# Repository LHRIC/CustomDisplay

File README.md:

# Custom Display

##Purpose

Custom Display is a driver information display for the car, built on an STM32H7 microcontroller with a Riverdi LCD. The STM32 reads live data from the Haltech ECU over the car's CAN bus and renders it on-screen using [TouchGFX](https://support.touchgfx.com/docs/introduction/what-is-touchgfx), an embedded graphics library for STM32.

**Display hardware:** [https://riverdi.com/product/5-inch-tft-lcd-screen-stm32u5-embedded-display-rvt50hqsfwn01?srsltid=AfmBOoq_PbYSuQUkMhpmtfA5kOqO7L9fX0RrjbtiRxhyNDaXJeP7M8Rh](#)  
> 

---

## Overview

| Detail | Value |
|---|---|
| Microcontroller | STM32H7 |
| Display | Riverdi LCD |
| Graphics Library | TouchGFX |
| Language | C / C++ |
| RTOS | None (simplified loop via `Model::tick`) |
| Data Source | ECU via CAN bus |

---

## Architecture

All code is written in C style but integrates with TouchGFX, a C++ library. There is no RTOS — the update loop runs entirely inside `Model::tick` for simplicity.

### Data Flow

```
CAN Bus (mostly ECU though it can be anything on CAN bus)
    │
    ▼
CAN Interrupt (main.c)
    │  updates
    ▼
can_types.cpp  ──  UI data elements & handlers
-----
Model.cpp      ──  data update tick
    │
    ▼
Screen1Presenter.cpp
    │
    ▼
Screen1View.cpp  ──  UI element rendering
```

### Key Files

| File | Role |
|---|---|
| `main.c` | CAN interrupt setup; `RxFifo0Callback` routes incoming CAN frames |
| `can_types.hpp` | Declares CAN value types, IDs, default values, etc|
| `can_types.cpp` | Defines CAN values and the `CAN_value_ptrs` array |
| `Model.cpp` | Polls updated CAN data each tick and forwards to presenter |
| `Screen1Presenter.cpp` | Mediates between model and view |
| `Screen1View.cpp` | Updates UI elements; handles special visual logic |

---

## Contributing

The TouchGFX tutorials and docs are pretty good for understanding how it works. Also, I used CubeMX to generate code, TouchGFX Designer to generate UI code, CMake to build, and VSCode Arm Cortex Debug for flash/debug.

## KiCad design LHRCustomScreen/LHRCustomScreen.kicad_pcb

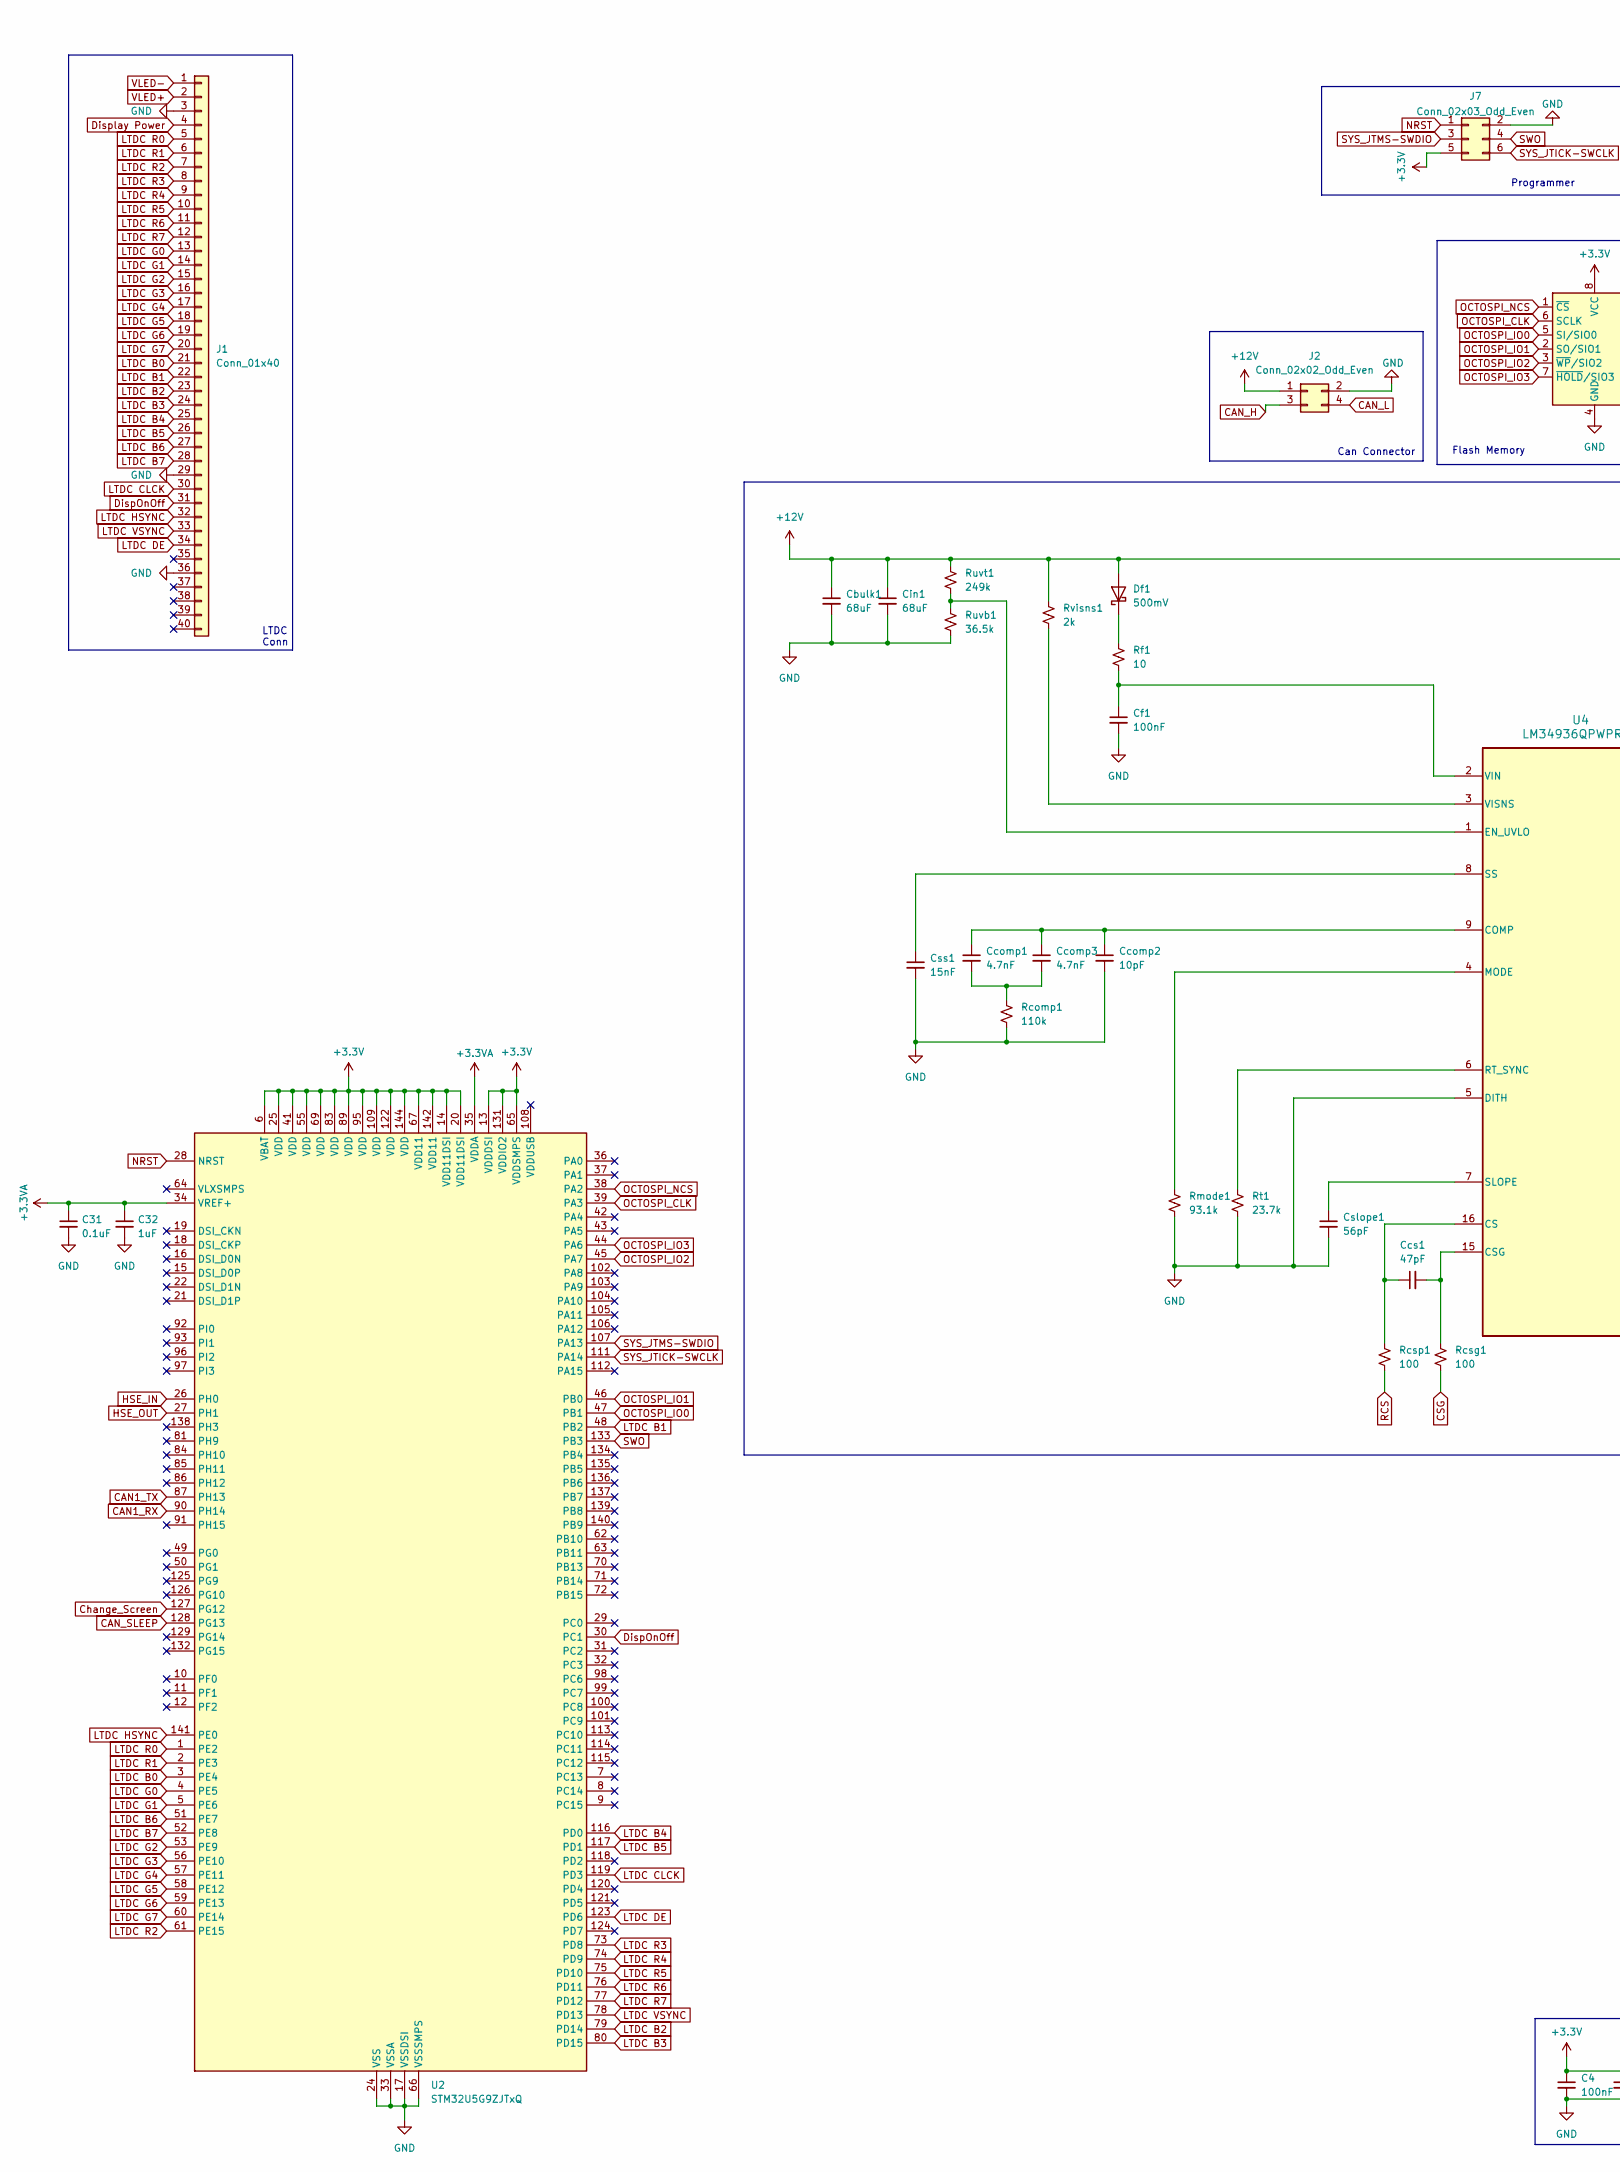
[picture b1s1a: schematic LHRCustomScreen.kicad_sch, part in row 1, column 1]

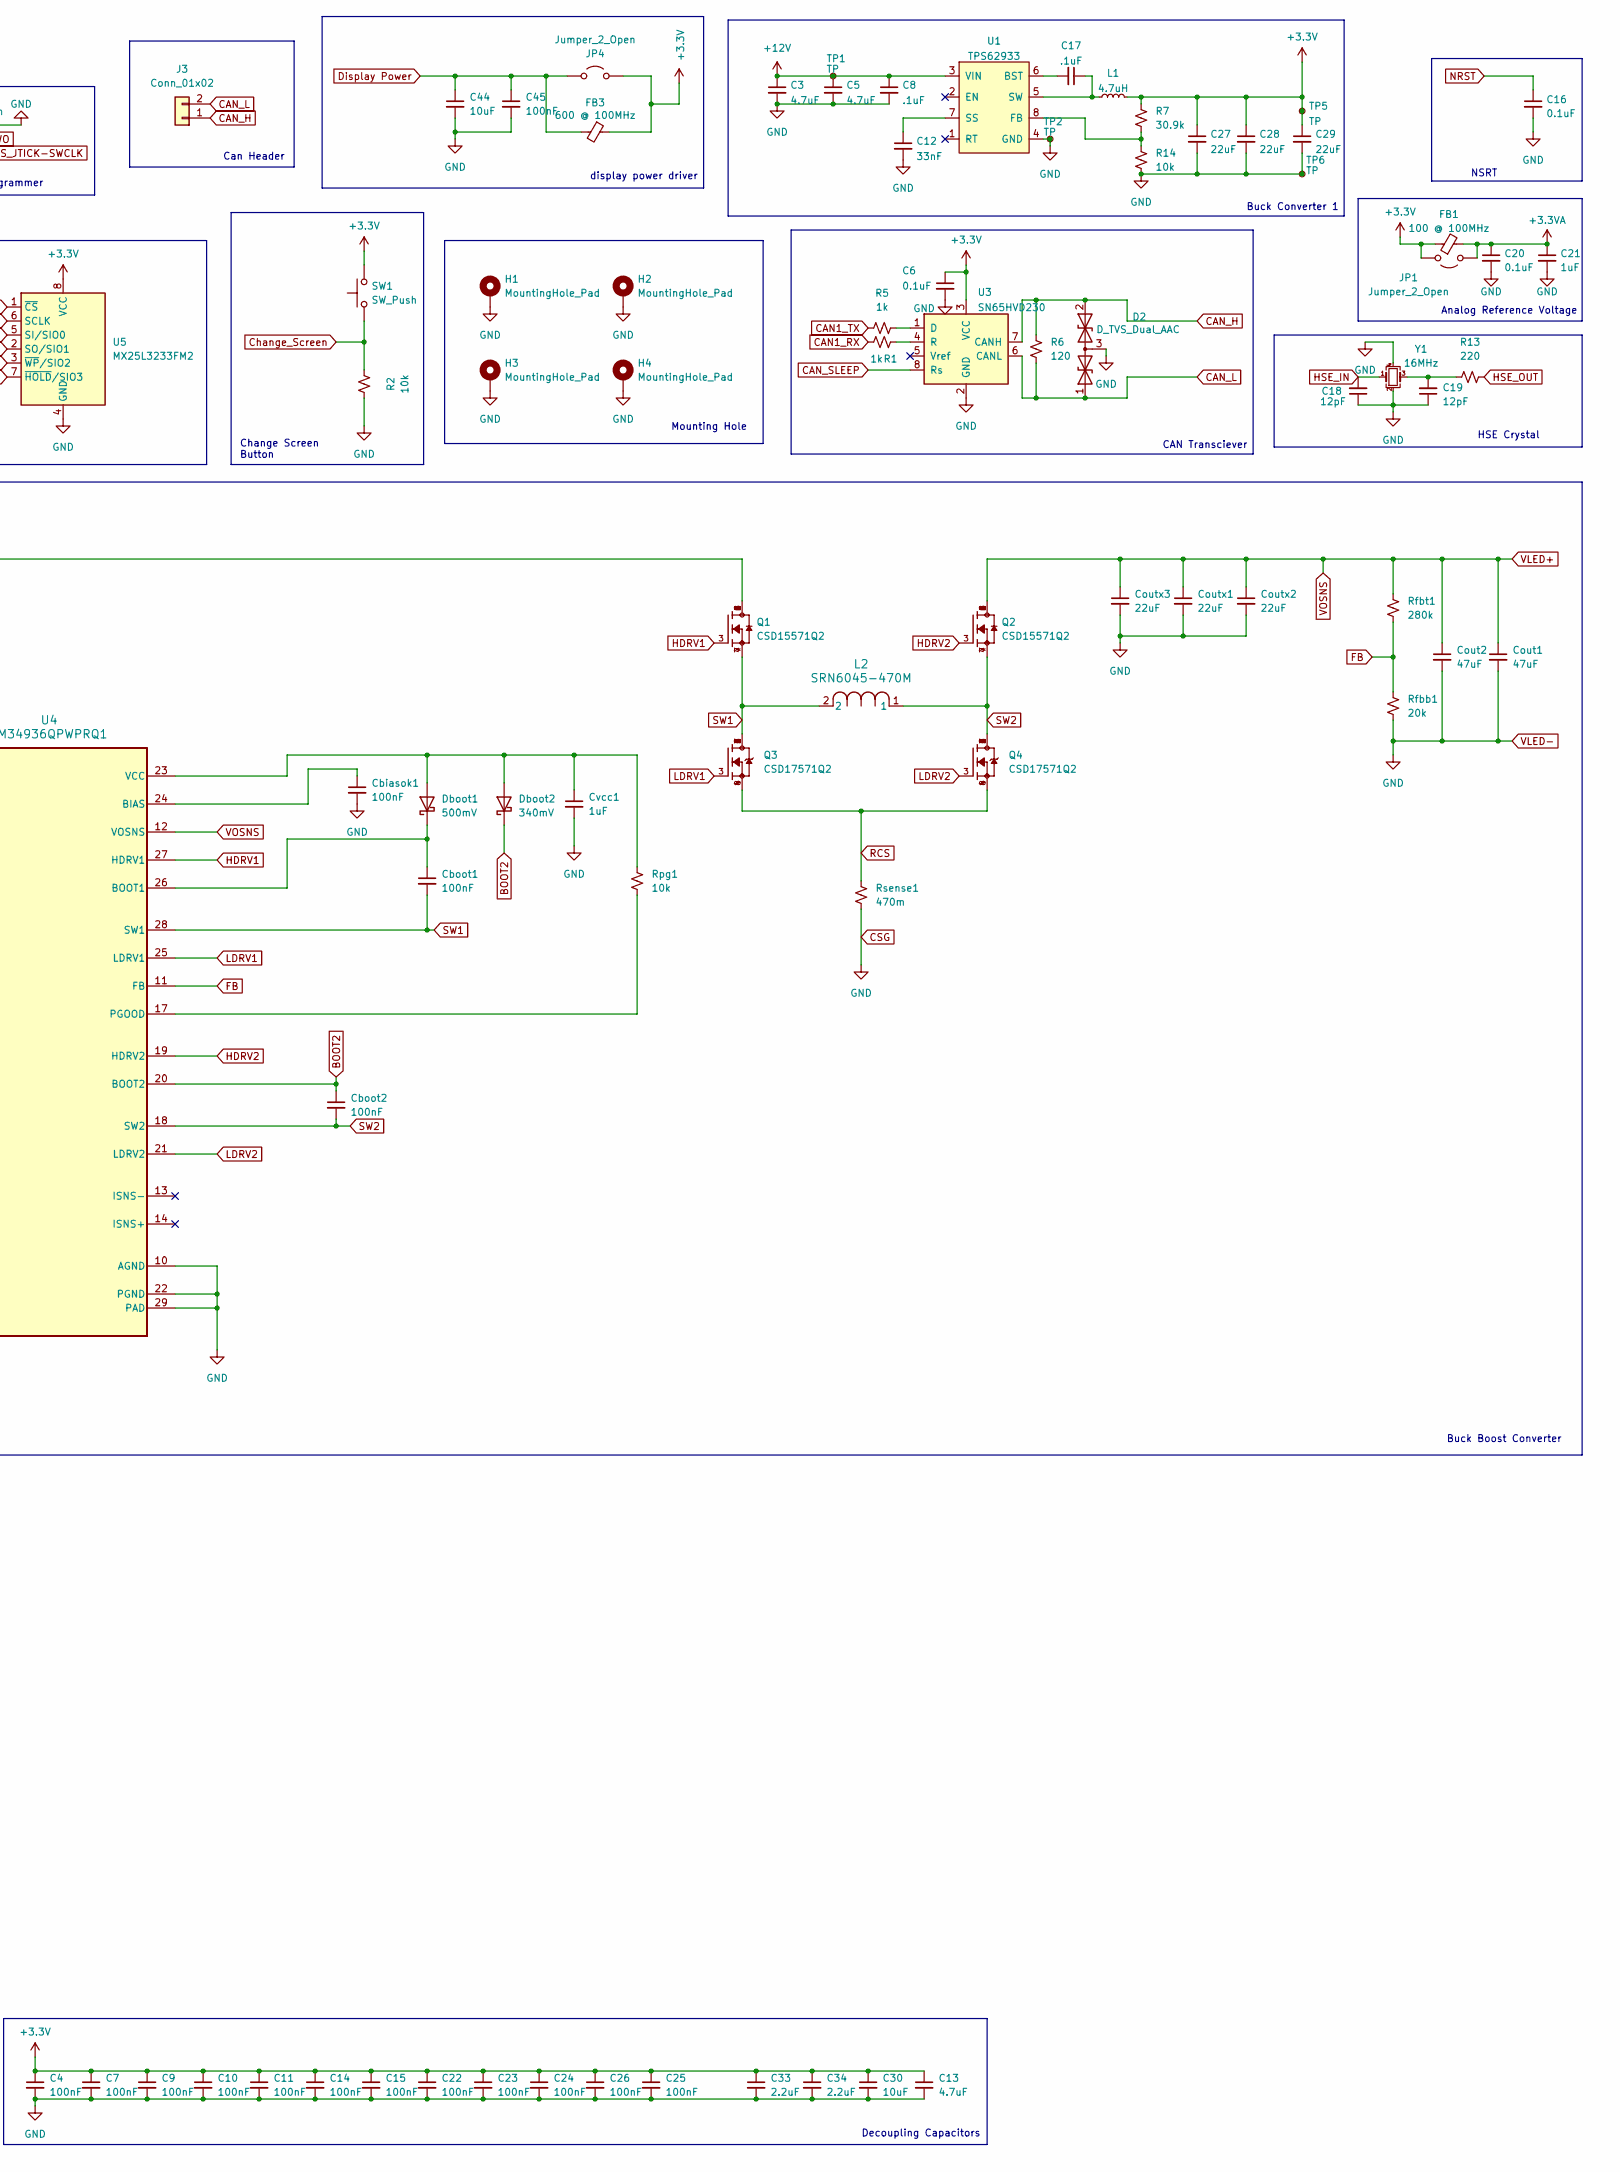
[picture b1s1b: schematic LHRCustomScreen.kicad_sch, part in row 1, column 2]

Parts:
C3, C5, C13: 4.7uF; C_0805_2012Metric
C4, C7, C9, C10, C11, C14, C15, C22, C23, C24, C25, C26, C45: 100nF; C_0603_1608Metric
C6, C20, C31: 0.1uF; C_0603_1608Metric
C8, C17: .1uF; C_0603_1608Metric
C12: 33nF; C_0603_1608Metric
C16: 0.1uF; C_0402_1005Metric
C18, C19: 12pF; C_0402_1005Metric
C21, C32: 1uF; C_0603_1608Metric
C27, C28, C29: 22uF; C_0805_2012Metric
C30, C44: 10uF; C_0805_2012Metric
C33, C34: 2.2uF; C_0603_1608Metric
Cbiasok1: 100nF; C_0805_2012Metric
Cboot1, Cboot2: 100nF; C_0603_1608Metric
Cbulk1: 68uF; PCAP_6.3x7.7-ELECT_NCA
Ccomp1, Ccomp3: 4.7nF; C_0201_0603Metric
Ccomp2: 10pF; C_0805_2012Metric
Ccs1: 47pF; C_0603_1608Metric
Cf1: 100nF; C_0603_1608Metric
Cin1: 68uF; PCAP_6.3x7.7-ELECT_NCA
Cout1, Cout2: 47uF; CAPC3225X270N
Coutx1, Coutx2, Coutx3: 22uF; C_0805_2012Metric
Cslope1: 56pF; C_0201_0603Metric
Css1: 15nF; C_0603_1608Metric
Cvcc1: 1uF; C_0603_1608Metric
D2: D_TVS_Dual_AAC; SOT-23
Dboot1: 500mV; DO-214AC_VIS
Dboot2: 340mV; DIOM3616X98N
Df1: 500mV; DO-214AC_VIS
FB1: 100 @ 100MHz; C_0402_1005Metric
FB3: 600 @ 100MHz; BEADC1608X95N
H1, H2, H3, H4: MountingHole_Pad; MountingHole_3.2mm_M3_DIN965_Pad_TopBottom
J1: Conn_01x40; FPC_40
J2: Conn_02x02_Odd_Even; ATM15-4P-BM03
J3: Conn_01x02; PinHeader_1x02_P2.54mm_Vertical
J7: Conn_02x03_Odd_Even; Molex_Micro-Fit_3.0_43045-0612_2x03_P3.00mm_Vertical
JP1, JP4: Jumper_2_Open; SolderJumper-2_P1.3mm_Bridged_RoundedPad1.0x1.5mm
L1: 4.7uH; SRU8043-4R7Y
L2: SRN6045-470M; IND_BOURNS_SRN6045
Q1, Q2: CSD15571Q2; TRANS_CSD15571Q2; PARTREV D
Q3, Q4: CSD17571Q2; TRANS_CSD17571Q2; PARTREV A
R1, R5: 1k; R_0603_1608Metric
R2, R14: 10k; R_0603_1608Metric
R6: 120; R_0603_1608Metric
R7: 30.9k; R_0603_1608Metric
R13: 220; R_0603_1608Metric
Rcomp1: 110k; R_0402_1005Metric
Rcsg1: 100; R_0603_1608Metric
Rcsp1: 100; R_0603_1608Metric
Rf1: 10; R_0603_1608Metric
Rfbb1: 20k; R_0603_1608Metric
Rfbt1: 280k; R_0603_1608Metric
Rmode1: 93.1k; R_0603_1608Metric
Rpg1: 10k; R_0603_1608Metric
Rsense1: 470m; R_0603_1608Metric
Rt1: 23.7k; R_0603_1608Metric
Ruvb1: 36.5k; R_0603_1608Metric
Ruvt1: 249k; R_0603_1608Metric
Rvisns1: 2k; R_0402_1005Metric
SW1: SW_Push; SW_PUSH_6mm
TP1, TP2, TP5, TP6: TP; TestPoint_Pad_D2.0mm
U1: TPS62933; SOT-583
U2: STM32U5G9ZJTxQ; LQFP-144_20x20mm_P0.5mm
U3: SN65HVD230; SOIC-8_3.9x4.9mm_P1.27mm
U4: LM34936QPWPRQ1; PWP0028C_N
U5: MX25L3233FM2; SOIC-8_5.3x5.3mm_P1.27mm
Y1: 16MHz; Crystal_SMD_3225-4Pin_3.2x2.5mm

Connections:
+3.3V: C4.1, C6.1, C7.1, C9.1, C10.1, C11.1, C13.1, C14.1, C15.1, C22.1, C23.1, C24.1, C25.1, C26.1, C27.1, C28.1, C29.1, C30.1, C33.1, C34.1, FB1.1, FB3.1, J7.5, JP1.2 (B), JP4.2 (B), L1.2, R7.1, SW1.2, TP5.1, U2.6 (VBAT), U2.13 (VDDDSI), U2.14 (VDD11DSI), U2.20 (VDD11DSI), U2.25 (VDD), U2.41 (VDD), U2.55 (VDD), U2.65 (VDDSMPS), U2.67 (VDD11), U2.69 (VDD), U2.83 (VDD), U2.89 (VDD), U2.95 (VDD), U2.109 (VDD), U2.122 (VDD), U2.131 (VDDIO2), U2.142 (VDD11), U2.144 (VDD), U3.3 (VCC), U5.8 (VCC); also elsewhere on the board
+3.3VA: C20.1, C21.1, C31.1, C32.1, FB1.2, JP1.1 (A), U2.34 (VREF+), U2.35 (VDDA)
+12V: C3.1, C5.1, C8.1, Cbulk1.1, Cin1.1, Df1.2 (A), J2.1, Q1.1, Q1.2, Q1.5, Q1.6, Q1.8, Ruvt1.1, Rvisns1.1, TP1.1, U1.3 (VIN); also elsewhere on the board
BOOT2: Cboot2.1, Dboot2.1 (K), U4.20 (BOOT2)
CAN1_RX: R1.2, U2.90 (PH14)
CAN1_TX: R5.1, U2.87 (PH13)
CAN_H: D2.2 (A2), J2.3, J3.1, R6.2, U3.7 (CANH)
CAN_L: D2.1 (A1), J2.4, J3.2, R6.1, U3.6 (CANL)
CAN_SLEEP: U2.128 (PG13), U3.8 (Rs)
CSG: C3.2, C4.2, C5.2, C6.2, C7.2, C8.2, C9.2, C10.2, C11.2, C12.2, C13.2, C14.2, C15.2, C16.2, C18.1, C19.1, C20.2, C21.2, C22.2, C23.2, C24.2, C25.2, C26.2, C27.2, C28.2, C29.2, C30.2, C31.2, C32.2, C33.2, C34.2, C44.2, C45.2, Cbiasok1.2, Cbulk1.2, Ccomp2.2, Cf1.2, Cin1.2, Cout1.2, Cout2.2, Coutx1.2, Coutx2.2, Coutx3.2, Cslope1.2, Css1.2, Cvcc1.2, D2.3 (common), H1.1, H2.1, H3.1, H4.1, J1.1, J1.3, J1.29, J1.36, J2.2, J7.2, R2.1, R14.2, Rcomp1.2, Rcsg1.2, Rfbb1.2, Rmode1.2, Rsense1.2, Rt1.2, Ruvb1.2, TP2.1, TP6.1, U1.4 (GND), U2.17 (VSSDSI), U2.23 (VSSDSI), U2.24 (VSS), U2.33 (VSSA), U2.40 (VSS), U2.54 (VSS), U2.66 (VSSSMPS), U2.68 (VSS), U2.82 (VSS), U2.88 (VSS), U2.94 (VSS), U2.110 (VSS), U2.130 (VSS), U2.143 (VSS), U3.2 (GND), U4.5 (DITH), U4.10 (AGND), U4.22 (PGND), U4.29 (PAD), U5.4 (GND), Y1.2, Y1.4; also elsewhere on the board
Change_Screen: R2.2, SW1.1, U2.127 (PG12)
DispOnOff: J1.31, U2.30 (PC1)
Display Power: C44.1, C45.1, FB3.2, J1.4, JP4.1 (A)
FB: Rfbb1.1, Rfbt1.2, U4.11 (FB)
HDRV1: Q1.3, U4.27 (HDRV1)
HDRV2: Q2.3, U4.19 (HDRV2)
HSE_IN: C18.2, U2.26 (PH0), Y1.1
HSE_OUT: R13.2, U2.27 (PH1)
LDRV1: Q3.3, U4.25 (LDRV1)
LDRV2: Q4.3, U4.21 (LDRV2)
LTDC B0: J1.21, U2.3 (PE4)
LTDC B1: J1.22, U2.48 (PB2)
LTDC B2: J1.23, U2.79 (PD14)
LTDC B3: J1.24, U2.80 (PD15)
LTDC B4: J1.25, U2.116 (PD0)
LTDC B5: J1.26, U2.117 (PD1)
LTDC B6: J1.27, U2.51 (PE7)
LTDC B7: J1.28, U2.52 (PE8)
LTDC CLCK: J1.30, U2.119 (PD3)
LTDC DE: J1.34, U2.123 (PD6)
LTDC G0: J1.13, U2.4 (PE5)
LTDC G1: J1.14, U2.5 (PE6)
LTDC G2: J1.15, U2.53 (PE9)
LTDC G3: J1.16, U2.56 (PE10)
LTDC G4: J1.17, U2.57 (PE11)
LTDC G5: J1.18, U2.58 (PE12)
LTDC G6: J1.19, U2.59 (PE13)
LTDC G7: J1.20, U2.60 (PE14)
LTDC HSYNC: J1.32, U2.141 (PE0)
LTDC R0: J1.5, U2.1 (PE2)
LTDC R1: J1.6, U2.2 (PE3)
LTDC R2: J1.7, U2.61 (PE15)
LTDC R3: J1.8, U2.73 (PD8)
LTDC R4: J1.9, U2.74 (PD9)
LTDC R5: J1.10, U2.75 (PD10)
LTDC R6: J1.11, U2.76 (PD11)
LTDC R7: J1.12, U2.77 (PD12)
LTDC VSYNC: J1.33, U2.78 (PD13)
NRST: C16.1, J7.1, U2.28 (NRST)
unnamed: C19.2, R13.1, Y1.3
unnamed: Ccomp1.2, Ccomp3.2, Rcomp1.1
unnamed: Cvcc1.1, Dboot1.2 (A), Dboot2.2 (A), Rpg1.1, U4.23 (VCC)
unnamed: Cboot1.1, Dboot1.1 (K), U4.26 (BOOT1)
unnamed: Df1.1 (K), Rf1.1
unnamed: C17.2, U1.6 (BST)
unnamed: R7.2, R14.1, U1.8 (FB)
unnamed: C12.1, U1.7 (SS)
unnamed: C17.1, L1.1, U1.5 (SW)
unnamed: R5.2, U3.1 (D)
unnamed: R1.1, U3.4 (R)
unnamed: Cbiasok1.1, U4.24 (BIAS)
unnamed: Ccomp1.1, Ccomp2.1, Ccomp3.1, U4.9 (COMP)
unnamed: Ccs1.1, Rcsp1.1, U4.16 (CS)
unnamed: Ccs1.2, Rcsg1.1, U4.15 (CSG)
unnamed: Ruvb1.1, Ruvt1.2, U4.1 (EN_UVLO)
unnamed: Rmode1.1, U4.4 (MODE)
unnamed: Rpg1.2, U4.17 (PGOOD)
unnamed: Rt1.1, U4.6 (RT_SYNC)
unnamed: Cslope1.1, U4.7 (SLOPE)
unnamed: Css1.1, U4.8 (SS)
unnamed: Cf1.1, Rf1.2, U4.2 (VIN)
unnamed: Rvisns1.2, U4.3 (VISNS)
OCTOSPI_CLK: U2.39 (PA3), U5.6 (SCLK)
OCTOSPI_IO0: U2.47 (PB1), U5.5 (SI/SIO0)
OCTOSPI_IO1: U2.46 (PB0), U5.2 (SO/SIO1)
OCTOSPI_IO2: U2.45 (PA7), U5.3 (~WP/SIO2)
OCTOSPI_IO3: U2.44 (PA6), U5.7 (~HOLD/SIO3)
OCTOSPI_NCS: U2.38 (PA2), U5.1 (~CS)
RCS: Q3.4, Q3.8, Q4.4, Q4.8, Rcsp1.2, Rsense1.1
SW1: Cboot1.2, L2.2, Q1.4, Q1.7, Q3.1, Q3.2, Q3.5, Q3.6, Q3.7, U4.28 (SW1)
SW2: Cboot2.2, L2.1, Q2.4, Q2.7, Q4.1, Q4.2, Q4.5, Q4.6, Q4.7, U4.18 (SW2)
SWO: J7.4, U2.133 (PB3)
SYS_JTICK-SWCLK: J7.6, U2.111 (PA14)
SYS_JTMS-SWDIO: J7.3, U2.107 (PA13)
VLED+: Cout1.1, Cout2.1, Coutx1.1, Coutx2.1, Coutx3.1, J1.2, Q2.1, Q2.2, Q2.5, Q2.6, Q2.8, Rfbt1.1, U4.12 (VOSNS)

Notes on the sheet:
Buck Boost Converter
Can Header
Can Connector
display power driver
Mounting Hole
Programmer
LTDC Conn
NSRT
HSE Crystal
Decoupling Capacitors
Flash Memory
CAN Transciever
Analog Reference Voltage
Buck Converter 1
Change Screen Button

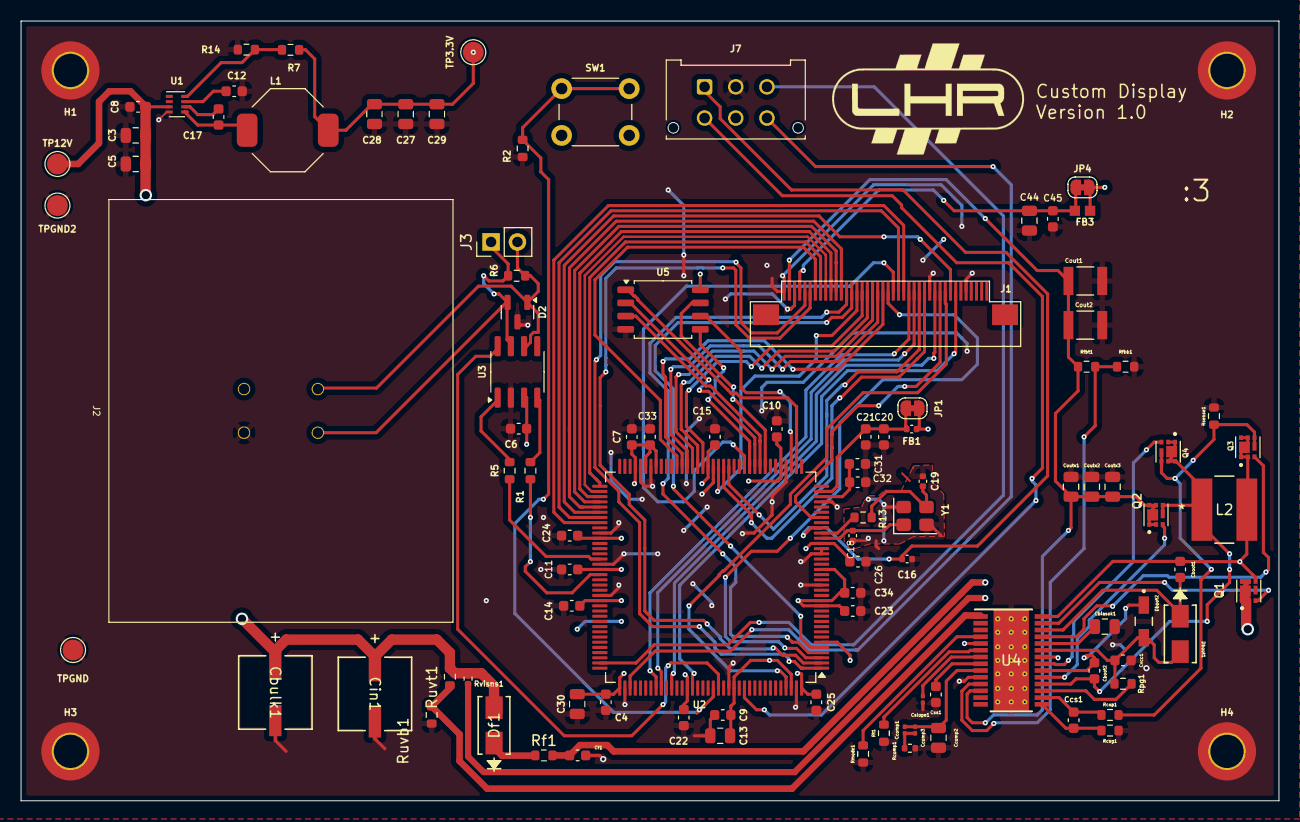
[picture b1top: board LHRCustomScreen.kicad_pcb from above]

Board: 4 copper layers, 121.0 x 75.0 mm, 105 parts (0 on the bottom side), 85 nets.

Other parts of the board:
TP3.3V, TP12V: TP; TestPoint_Pad_D2.0mm
TPGND, TPGND2: TP; TestPoint_Pad_D2.0mm

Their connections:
+3.3V: TP3.3V.1; also elsewhere on the board
+12V: TP12V.1; also elsewhere on the board
CSG: TPGND.1, TPGND2.1; also elsewhere on the board

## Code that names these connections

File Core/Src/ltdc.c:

/* USER CODE BEGIN Header */
/**
  ******************************************************************************
  * @file    ltdc.c
  * @brief   This file provides code for the configuration
  *          of the LTDC instances.
  ******************************************************************************
  * @attention
  *
  * Copyright (c) 2024 STMicroelectronics.
  * All rights reserved.
  *
  * This software is licensed under terms that can be found in the LICENSE file
  * in the root directory of this software component.
  * If no LICENSE file comes with this software, it is provided AS-IS.
  *
  ******************************************************************************
  */
/* USER CODE END Header */
/* Includes ------------------------------------------------------------------*/
#include "ltdc.h"

/* USER CODE BEGIN 0 */

/* USER CODE END 0 */

LTDC_HandleTypeDef hltdc;

/* LTDC init function */
void MX_LTDC_Init(void)
{

  /* USER CODE BEGIN LTDC_Init 0 */

  /* USER CODE END LTDC_Init 0 */

  LTDC_LayerCfgTypeDef pLayerCfg = {0};

  /* USER CODE BEGIN LTDC_Init 1 */

  /* USER CODE END LTDC_Init 1 */
  hltdc.Instance = LTDC;
  hltdc.Init.HSPolarity = LTDC_HSPOLARITY_AL;
  hltdc.Init.VSPolarity = LTDC_VSPOLARITY_AL;
  hltdc.Init.DEPolarity = LTDC_DEPOLARITY_AL;
  hltdc.Init.PCPolarity = LTDC_PCPOLARITY_IPC;
  hltdc.Init.HorizontalSync = 3;
  hltdc.Init.VerticalSync = 3;
  hltdc.Init.AccumulatedHBP = 11;
  hltdc.Init.AccumulatedVBP = 11;
  hltdc.Init.AccumulatedActiveW = 811;
  hltdc.Init.AccumulatedActiveH = 491;
  hltdc.Init.TotalWidth = 819;
  hltdc.Init.TotalHeigh = 499;
  hltdc.Init.Backcolor.Blue = 0;
  hltdc.Init.Backcolor.Green = 0;
  hltdc.Init.Backcolor.Red = 0;
  if (HAL_LTDC_Init(&hltdc) != HAL_OK)
  {
    Error_Handler();
  }
  pLayerCfg.WindowX0 = 0;
  pLayerCfg.WindowX1 = 800;
  pLayerCfg.WindowY0 = 0;
  pLayerCfg.WindowY1 = 480;
  pLayerCfg.PixelFormat = LTDC_PIXEL_FORMAT_RGB888;
  pLayerCfg.Alpha = 255;
  pLayerCfg.Alpha0 = 0;
  pLayerCfg.BlendingFactor1 = LTDC_BLENDING_FACTOR1_CA;
  pLayerCfg.BlendingFactor2 = LTDC_BLENDING_FACTOR2_CA;
  pLayerCfg.FBStartAdress = 0x20000000;
  pLayerCfg.ImageWidth = 800;
  pLayerCfg.ImageHeight = 480;
  pLayerCfg.Backcolor.Blue = 0;
  pLayerCfg.Backcolor.Green = 0;
  pLayerCfg.Backcolor.Red = 0;
  if (HAL_LTDC_ConfigLayer(&hltdc, &pLayerCfg, 0) != HAL_OK)
  {
    Error_Handler();
  }
  /* USER CODE BEGIN LTDC_Init 2 */

  /* USER CODE END LTDC_Init 2 */

}

void HAL_LTDC_MspInit(LTDC_HandleTypeDef* ltdcHandle)
{

  GPIO_InitTypeDef GPIO_InitStruct = {0};
  RCC_PeriphCLKInitTypeDef PeriphClkInit = {0};
  if(ltdcHandle->Instance==LTDC)
  {
  /* USER CODE BEGIN LTDC_MspInit 0 */

  /* USER CODE END LTDC_MspInit 0 */

  /** Initializes the peripherals clock
  */
    PeriphClkInit.PeriphClockSelection = RCC_PERIPHCLK_LTDC;
    PeriphClkInit.LtdcClockSelection = RCC_LTDCCLKSOURCE_PLL2;
    PeriphClkInit.PLL2.PLL2Source = RCC_PLLSOURCE_HSE;
    PeriphClkInit.PLL2.PLL2M = 4;
    PeriphClkInit.PLL2.PLL2N = 129;
    PeriphClkInit.PLL2.PLL2P = 8;
    PeriphClkInit.PLL2.PLL2Q = 8;
    PeriphClkInit.PLL2.PLL2R = 20;
    PeriphClkInit.PLL2.PLL2RGE = RCC_PLLVCIRANGE_0;
    PeriphClkInit.PLL2.PLL2FRACN = 0;
    PeriphClkInit.PLL2.PLL2ClockOut = RCC_PLL2_DIVR;
    if (HAL_RCCEx_PeriphCLKConfig(&PeriphClkInit) != HAL_OK)
    {
      Error_Handler();
    }

    /* LTDC clock enable */
    __HAL_RCC_LTDC_CLK_ENABLE();

    __HAL_RCC_GPIOE_CLK_ENABLE();
    __HAL_RCC_GPIOD_CLK_ENABLE();
    __HAL_RCC_GPIOC_CLK_ENABLE();
    __HAL_RCC_GPIOG_CLK_ENABLE();
    __HAL_RCC_GPIOF_CLK_ENABLE();
    /**LTDC GPIO Configuration
    PE0     ------> LTDC_HSYNC
    PD3     ------> LTDC_CLK
    PD1     ------> LTDC_B5
    PC6     ------> LTDC_R0
    PD0     ------> LTDC_B4
    PG6     ------> LTDC_R1
    PD15     ------> LTDC_B3
    PD11     ------> LTDC_R6
    PF13     ------> LTDC_B1
    PE8     ------> LTDC_B7
    PE13     ------> LTDC_G6
    PD12     ------> LTDC_R7
    PF12     ------> LTDC_B0
    PE7     ------> LTDC_B6
    PE15     ------> LTDC_R2
    PE12     ------> LTDC_G5
    PD8     ------> LTDC_R3
    PD13     ------> LTDC_VSYNC
    PD14     ------> LTDC_B2
    PF11     ------> LTDC_DE
    PF15     ------> LTDC_G1
    PE9     ------> LTDC_G2
    PE10     ------> LTDC_G3
    PE11     ------> LTDC_G4
    PD10     ------> LTDC_R5
    PD9     ------> LTDC_R4
    PF14     ------> LTDC_G0
    PE14     ------> LTDC_G7
    */
    GPIO_InitStruct.Pin = GPIO_PIN_0|GPIO_PIN_8|GPIO_PIN_13|GPIO_PIN_7
                          |GPIO_PIN_15|GPIO_PIN_12|GPIO_PIN_9|GPIO_PIN_10
                          |GPIO_PIN_11|GPIO_PIN_14;
    GPIO_InitStruct.Mode = GPIO_MODE_AF_PP;
    GPIO_InitStruct.Pull = GPIO_NOPULL;
    GPIO_InitStruct.Speed = GPIO_SPEED_FREQ_VERY_HIGH;
    GPIO_InitStruct.Alternate = GPIO_AF8_LTDC;
    HAL_GPIO_Init(GPIOE, &GPIO_InitStruct);

    GPIO_InitStruct.Pin = GPIO_PIN_3|GPIO_PIN_1|GPIO_PIN_0|GPIO_PIN_15
                          |GPIO_PIN_11|GPIO_PIN_12|GPIO_PIN_8|GPIO_PIN_13
                          |GPIO_PIN_14|GPIO_PIN_10|GPIO_PIN_9;
    GPIO_InitStruct.Mode = GPIO_MODE_AF_PP;
    GPIO_InitStruct.Pull = GPIO_NOPULL;
    GPIO_InitStruct.Speed = GPIO_SPEED_FREQ_VERY_HIGH;
    GPIO_InitStruct.Alternate = GPIO_AF8_LTDC;
    HAL_GPIO_Init(GPIOD, &GPIO_InitStruct);

    GPIO_InitStruct.Pin = GPIO_PIN_6;
    GPIO_InitStruct.Mode = GPIO_MODE_AF_PP;
    GPIO_InitStruct.Pull = GPIO_NOPULL;
    GPIO_InitStruct.Speed = GPIO_SPEED_FREQ_VERY_HIGH;
    GPIO_InitStruct.Alternate = GPIO_AF7_LTDC;
    HAL_GPIO_Init(GPIOC, &GPIO_InitStruct);

    GPIO_InitStruct.Pin = GPIO_PIN_6;
    GPIO_InitStruct.Mode = GPIO_MODE_AF_PP;
    GPIO_InitStruct.Pull = GPIO_NOPULL;
    GPIO_InitStruct.Speed = GPIO_SPEED_FREQ_VERY_HIGH;
    GPIO_InitStruct.Alternate = GPIO_AF7_LTDC;
    HAL_GPIO_Init(GPIOG, &GPIO_InitStruct);

    GPIO_InitStruct.Pin = GPIO_PIN_13|GPIO_PIN_12|GPIO_PIN_11|GPIO_PIN_15
                          |GPIO_PIN_14;
    GPIO_InitStruct.Mode = GPIO_MODE_AF_PP;
    GPIO_InitStruct.Pull = GPIO_NOPULL;
    GPIO_InitStruct.Speed = GPIO_SPEED_FREQ_VERY_HIGH;
    GPIO_InitStruct.Alternate = GPIO_AF8_LTDC;
    HAL_GPIO_Init(GPIOF, &GPIO_InitStruct);

    /* LTDC interrupt Init */
    HAL_NVIC_SetPriority(LTDC_IRQn, 5, 0);
    HAL_NVIC_EnableIRQ(LTDC_IRQn);
    HAL_NVIC_SetPriority(LTDC_ER_IRQn, 5, 0);
    HAL_NVIC_EnableIRQ(LTDC_ER_IRQn);
  /* USER CODE BEGIN LTDC_MspInit 1 */

  /* USER CODE END LTDC_MspInit 1 */
  }
}

void HAL_LTDC_MspDeInit(LTDC_HandleTypeDef* ltdcHandle)
{

  if(ltdcHandle->Instance==LTDC)
  {
  /* USER CODE BEGIN LTDC_MspDeInit 0 */

  /* USER CODE END LTDC_MspDeInit 0 */
    /* Peripheral clock disable */
    __HAL_RCC_LTDC_CLK_DISABLE();

    /**LTDC GPIO Configuration
    PE0     ------> LTDC_HSYNC
    PD3     ------> LTDC_CLK
    PD1     ------> LTDC_B5
    PC6     ------> LTDC_R0
    PD0     ------> LTDC_B4
    PG6     ------> LTDC_R1
    PD15     ------> LTDC_B3
    PD11     ------> LTDC_R6
    PF13     ------> LTDC_B1
    PE8     ------> LTDC_B7
    PE13     ------> LTDC_G6
    PD12     ------> LTDC_R7
    PF12     ------> LTDC_B0
    PE7     ------> LTDC_B6
    PE15     ------> LTDC_R2
    PE12     ------> LTDC_G5
    PD8     ------> LTDC_R3
    PD13     ------> LTDC_VSYNC
    PD14     ------> LTDC_B2
    PF11     ------> LTDC_DE
    PF15     ------> LTDC_G1
    PE9     ------> LTDC_G2
    PE10     ------> LTDC_G3
    PE11     ------> LTDC_G4
    PD10     ------> LTDC_R5
    PD9     ------> LTDC_R4
    PF14     ------> LTDC_G0
    PE14     ------> LTDC_G7
    */
    HAL_GPIO_DeInit(GPIOE, GPIO_PIN_0|GPIO_PIN_8|GPIO_PIN_13|GPIO_PIN_7
                          |GPIO_PIN_15|GPIO_PIN_12|GPIO_PIN_9|GPIO_PIN_10
                          |GPIO_PIN_11|GPIO_PIN_14);

    HAL_GPIO_DeInit(GPIOD, GPIO_PIN_3|GPIO_PIN_1|GPIO_PIN_0|GPIO_PIN_15
                          |GPIO_PIN_11|GPIO_PIN_12|GPIO_PIN_8|GPIO_PIN_13
                          |GPIO_PIN_14|GPIO_PIN_10|GPIO_PIN_9);

    HAL_GPIO_DeInit(GPIOC, GPIO_PIN_6);

    HAL_GPIO_DeInit(GPIOG, GPIO_PIN_6);

    HAL_GPIO_DeInit(GPIOF, GPIO_PIN_13|GPIO_PIN_12|GPIO_PIN_11|GPIO_PIN_15
                          |GPIO_PIN_14);

    /* LTDC interrupt Deinit */
    HAL_NVIC_DisableIRQ(LTDC_IRQn);
    HAL_NVIC_DisableIRQ(LTDC_ER_IRQn);
  /* USER CODE BEGIN LTDC_MspDeInit 1 */

  /* USER CODE END LTDC_MspDeInit 1 */
  }
}

/* USER CODE BEGIN 1 */

/* USER CODE END 1 */

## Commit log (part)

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2025-10-18 working CAN update screen
2025-10-18 Removed TouchGFX generated files
2025-10-18 updated UI
2025-10-19 working slow display solution
2025-10-21 readability and organization changes
2025-10-25 added scale and offset and more CAN functions
2025-10-26 working CAN interrupt and fps counter
2025-11-05 testing with diagnostics screen and user button (not working)
2025-11-15 working button and diagnostic screen switching
2025-11-22 weird flashing bug
2025-12-06 no changes
2026-01-22 Add project title to README
2026-03-06 PCB Design
    KiCad Design for Custom Display
2026-03-09 added 12v plane
    added 12v plane
2026-05-01 added generated UI and fixed RPM and fault init state
2026-05-12 added rpm and speed txt
2026-05-22 added readme
    added readme with some helpful info for understanding/modifying display
2026-05-22 added readme
